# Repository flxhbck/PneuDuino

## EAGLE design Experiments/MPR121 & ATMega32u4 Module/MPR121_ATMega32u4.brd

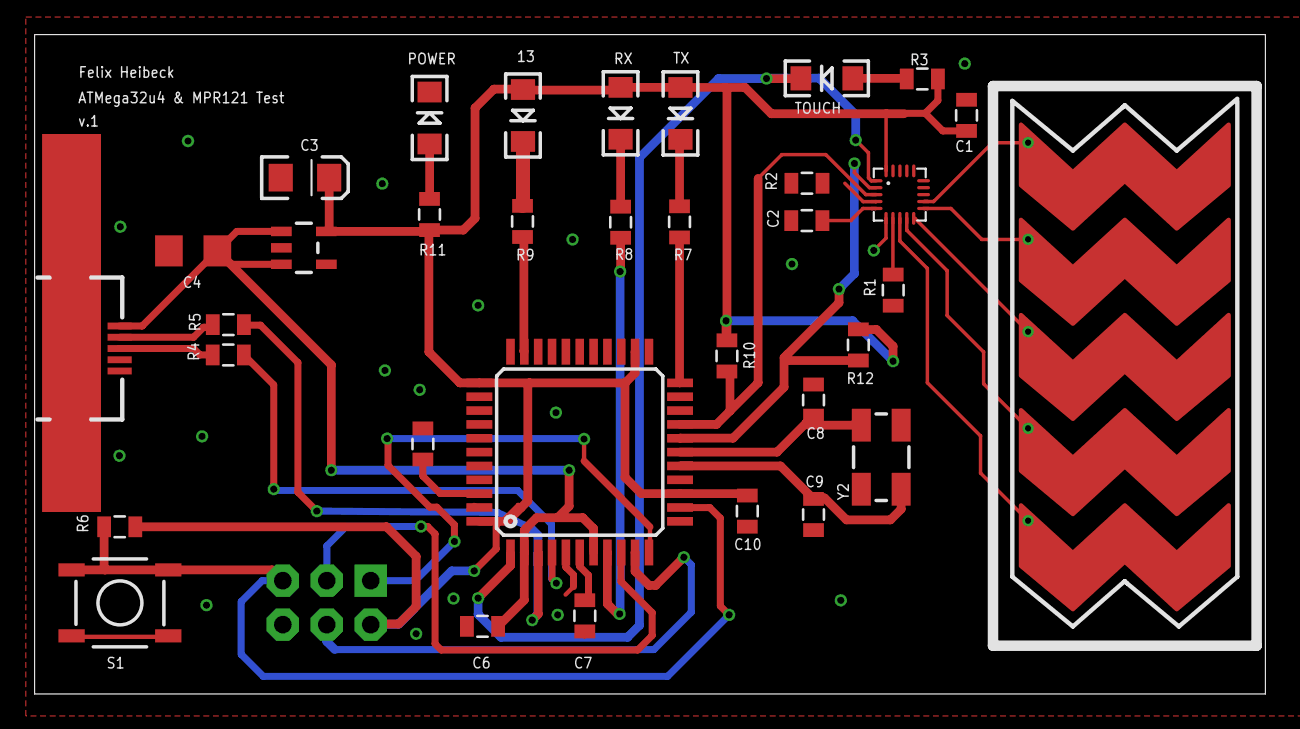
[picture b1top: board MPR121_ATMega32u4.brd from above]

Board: 2 copper layers, 71.1 x 38.1 mm, 35 parts (0 on the bottom side), 34 nets.

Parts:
13: Green; LED-1206
C1, C2, C5, C6, C7, C10: 0.1uF; 0805
C3: 2.2uF (Tant); EIA3216
C4: 10uF; 1206
C8, C9: 22pF; 0805
J1: AVR_SPI_PRG_6NS; 2X3-NS
POWER: Red; LED-1206
R1: 75k 1%; 0805
R2, R6: 10k; 0805
R3, R7, R8, R9: TBD; 0805
R4, R5: 22; 0805
R10, R11, R12: 1k; 0805
RX: Green; LED-1206
S1: TAC_SWITCHSMD; TACTILE-SWITCH-SMD
SL2: SLIDER_PASSIVE_5SEGREV; SLIDER_PASSIVE_5SEG_12MM_REV
TOUCH: Green; LED-1206
TX: Green; LED-1206
U1: SOT23-5
U2: USB-AB-MICRO-SMD
U$1: MPR121V2; QFN-20-0.4MM-V2
U$3: ATMEGA32U4TQFP-44; TQFP44
Y2: CRYSTAL-SMD-5X3

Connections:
+3V3: 13.A, C1.1, C3.A, C10.1, J1.2, R3.2, R6.2, R10.1, R11.2, R12.1, RX.A, TX.A, U1.5, U$1.20, U$3.14, U$3.24, U$3.34, U$3.44
+5V: C4.1, C6.1, U1.1, U1.3, U2.VBUS, U$3.2, U$3.7
ADDR: R2.2, U$1.4
D+: R4.2, U$3.4
D-: R5.2, U$3.3
GND: C1.2, C2.1, C3.C, C4.2, C5.1, C6.2, C7.1, C8.1, C9.1, C10.2, J1.6, POWER.C, R1.1, R2.1, S1.1, S1.2, U1.2, U2.GND, U$1.6, U$3.5, U$3.15, U$3.23, U$3.33, U$3.35, U$3.43
IRQ: TOUCH.C, U$1.1, U$3.1
MISO: J1.1, U$3.11
MOSI: J1.4, U$3.10
unnamed: C2.2, U$1.5
unnamed: R1.2, U$1.7
unnamed: SL2.SL5, U$1.8
unnamed: SL2.SL4, U$1.9
unnamed: SL2.SL3, U$1.10
unnamed: SL2.SL2, U$1.11
unnamed: SL2.SL1, U$1.12
unnamed: R3.1, TOUCH.A
unnamed: C7.2, U$3.6
unnamed: C9.2, U$3.16, Y2.1
unnamed: C8.2, U$3.17, Y2.3
unnamed: R5.1, U2.D-
unnamed: R4.1, U2.D+
unnamed: R8.2, U$3.8
unnamed: R7.2, U$3.22
unnamed: R8.1, RX.C
unnamed: R7.1, TX.C
unnamed: C5.2, U$3.42
unnamed: 13.C, R9.1
unnamed: R9.2, U$3.32
unnamed: POWER.A, R11.1
RESET: J1.5, R6.1, S1.3, S1.4, U$3.13
SCK: J1.3, U$3.9
SCL: R12.2, U$1.2, U$3.18
SDA: R10.2, U$1.3, U$3.19

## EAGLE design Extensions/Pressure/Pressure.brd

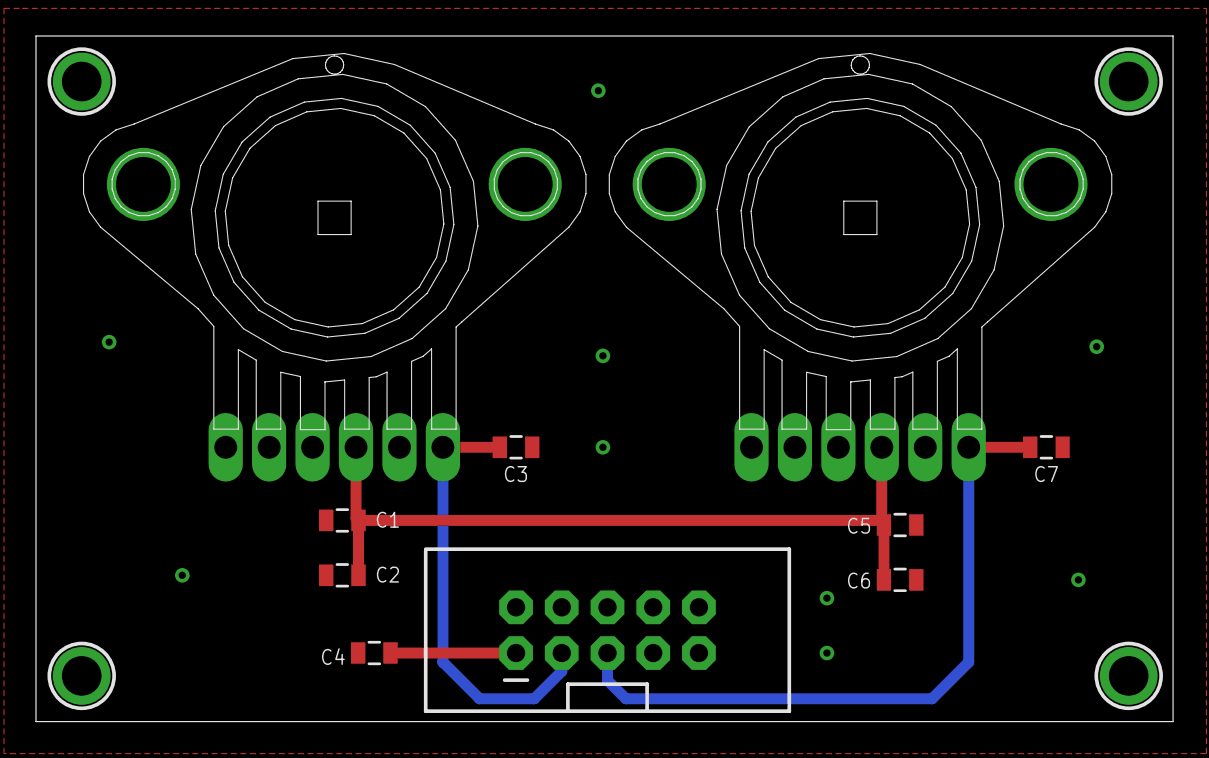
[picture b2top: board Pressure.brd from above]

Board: 2 copper layers, 63.2 x 38.1 mm, 14 parts (0 on the bottom side), 5 nets.

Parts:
C1, C5: 0.01uF; 0805
C2, C6: 1uF; 0805
C3, C7: 470pF; 0805
C4: 0.1uF; 0805
JP4: M05X2SHD; 2X5-SHROUDED
U$1, U$2: MPX5700; MPX5700ASX
U$9, U$10, U$11, U$12: MOUNTINGHOLE2.0; MOUNTINGHOLE_2.0_PLATED

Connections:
5V: C4.1, JP4.1
+5V: C1.1, C2.1, C5.1, C6.1, U$1.3, U$2.3
GND: C1.2, C2.2, C3.1, C4.2, C5.2, C6.2, C7.1, JP4.10, U$1.2, U$2.2
O0: C3.2, JP4.3, U$1.1
O1: C7.2, JP4.5, U$2.1

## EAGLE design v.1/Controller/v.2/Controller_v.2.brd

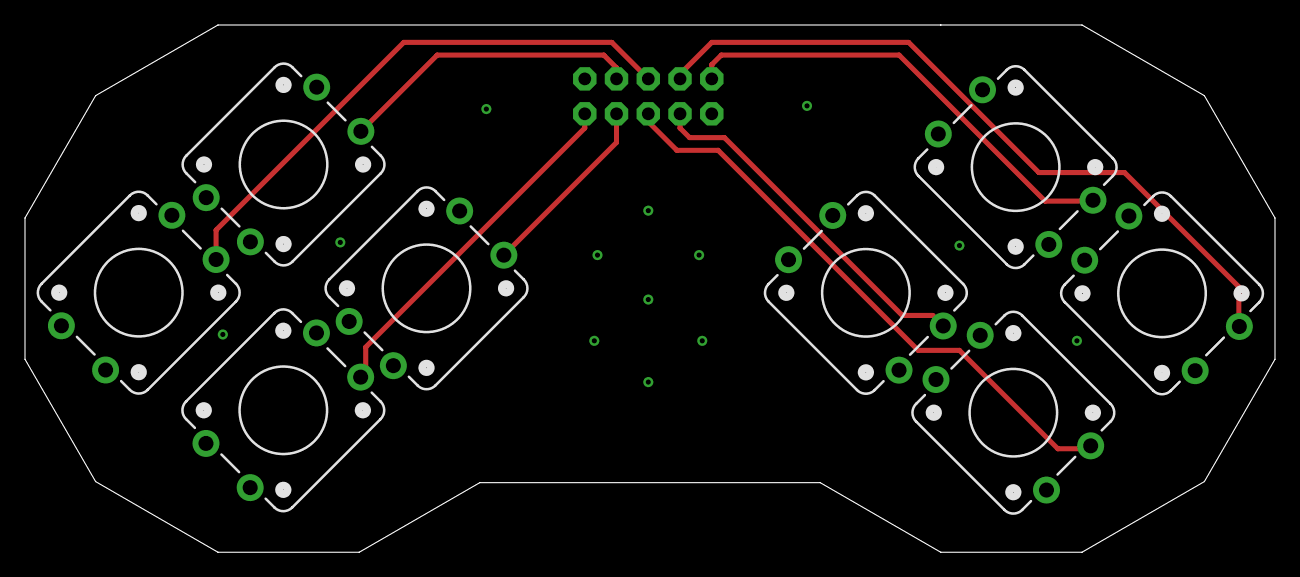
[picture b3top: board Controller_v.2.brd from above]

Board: 2 copper layers, 100.0 x 42.2 mm, 9 parts (1 on the bottom side), 9 nets.

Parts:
JP1: M05X2SHD_LOCK; 2X5-SHROUDED_LOCK
S1, S2, S3, S5, S6, S7, S8, S9: SWITCH-MOMENTARY-212MM; TACTILE-PTH-12MM

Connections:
1: JP1.3, S9.1
2: JP1.5, S2.1
3: JP1.7, S7.3
4: JP1.9, S5.3
5: JP1.2, S1.1
6: JP1.4, S3.1
7: JP1.6, S8.3
8: JP1.8, S6.3
GND: JP1.10, S1.3, S2.3, S3.3, S5.1, S6.1, S7.1, S8.1, S9.3

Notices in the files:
parts and their libraries:
SparkFun-Sensors: Licensing: CC v3.0 Share-Alike You are welcome to use this library for commercial purposes.
PatternAgents-TouchWidgets: License : http://creativecommons.org/licenses/by-sa/4.0/ (Creative Commons 4.0)
